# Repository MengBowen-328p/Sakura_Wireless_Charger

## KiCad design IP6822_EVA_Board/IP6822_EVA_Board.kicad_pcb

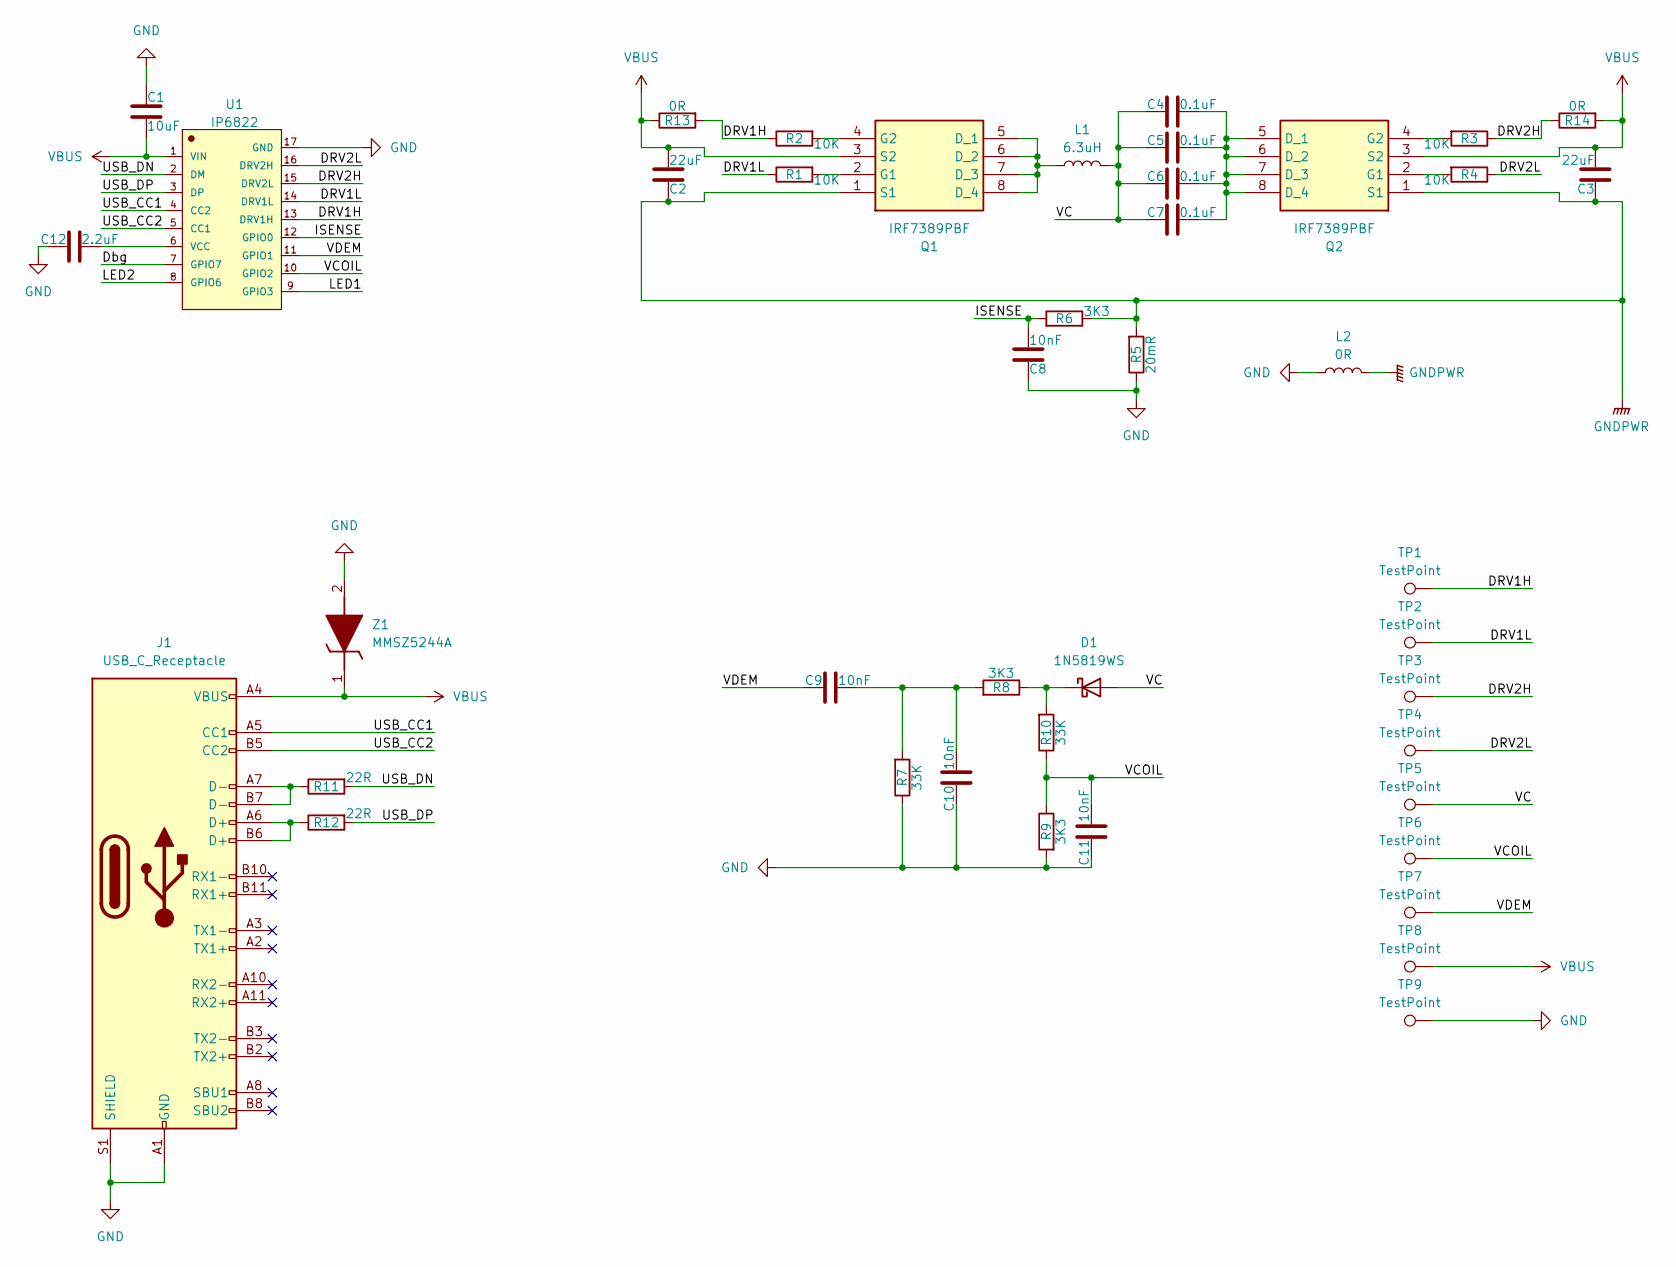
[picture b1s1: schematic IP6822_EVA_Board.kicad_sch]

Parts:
C1: 10uF; C_0603_1608Metric
C2, C3: 22uF; C_0603_1608Metric
C4, C5, C6, C7: 0.1uF; C_0805_2012Metric
C8, C9, C10, C11: 10nF; C_0603_1608Metric
C12: 2.2uF; C_0603_1608Metric
D1: 1N5819WS; D_SOD-323
J1: USB_C_Receptacle; USB_C_Receptacle_HCTL_HC-TYPE-C-16P-01A
L1: 6.3uH; L_2010_5025Metric
L2: 0R; L_0805_2012Metric
Q1, Q2: IRF7389PBF; SOIC127P600X175-8N; Manufacturer_Part_Number IRF7389PBF; Mouser Part Number 942-IRF7389PBF
R1, R2, R3, R4: 10K; R_0603_1608Metric
R5: 20mR; R_1206_3216Metric
R6, R8, R9: 3K3; R_0603_1608Metric
R7, R10: 33K; R_0603_1608Metric
R11, R12: 22R; R_0603_1608Metric
R13, R14: 0R; R_0603_1608Metric
TP1, TP2, TP3, TP4, TP5, TP6, TP7, TP8, TP9: TestPoint; TestPoint_Bridge_Pitch3.81mm_Drill1.3mm
U1: IP6822
Z1: MMSZ5244A; MMSZ5252B; Manufacturer_Part_Number MMSZ5244A

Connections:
/DRV1H: R2.1, R13.2, TP1.1, U1.13 (DRV1H)
/DRV1L: R1.1, TP2.1, U1.14 (DRV1L)
/DRV2H: R3.1, R14.1, TP3.1, U1.15 (DRV2L)
/DRV2L: R4.1, TP4.1, U1.16 (DRV2H)
/Dbg: U1.7 (GPIO7)
/ISENSE: C8.2, R6.2, U1.12 (GPIO0)
/LED1: U1.9 (GPIO3)
/LED2: U1.8 (GPIO6)
/USB_CC1: J1.A5 (CC1), U1.4 (CC2)
/USB_CC2: J1.B5 (CC2), U1.5 (CC1)
/USB_DN: R11.2, U1.2 (DM)
/USB_DP: R12.2, U1.3 (DP)
/VC: C4.1, C5.1, C6.1, C7.1, D1.2 (A), L1.2, TP5.1
/VCOIL: C11.2, R9.1, R10.1, TP6.1, U1.10 (GPIO2)
/VDEM: C9.1, TP7.1, U1.11 (GPIO1)
GND: C1.1, C8.1, C10.1, C11.1, C12.1, J1.A1 (GND), J1.A12 (GND), J1.B1 (GND), J1.B12 (GND), J1.S1 (SHIELD), L2.1, R5.1, R7.1, R9.2, TP9.1, U1.17 (GND), Z1.2 (A)
GNDPWR: C2.1, C3.1, L2.2, Q1.1 (S1), Q2.1 (S1), R5.2, R6.1
unnamed: C9.2, C10.2, R7.2, R8.2
unnamed: D1.1 (K), R8.1, R10.2
unnamed: J1.A6 (D+), J1.B6 (D+), R12.1
unnamed: J1.A7 (D-), J1.B7 (D-), R11.1
unnamed: L1.1, Q1.5 (D_1), Q1.6 (D_2), Q1.7 (D_3), Q1.8 (D_4)
unnamed: Q1.2 (G1), R1.2
unnamed: Q1.4 (G2), R2.2
unnamed: C4.2, C5.2, C6.2, C7.2, Q2.5 (D_1), Q2.6 (D_2), Q2.7 (D_3), Q2.8 (D_4)
unnamed: Q2.2 (G1), R4.2
unnamed: Q2.4 (G2), R3.2
unnamed: C12.2, U1.6 (VCC)
VBUS: C1.2, C2.2, C3.2, J1.A4 (VBUS), J1.A9 (VBUS), J1.B4 (VBUS), J1.B9 (VBUS), Q1.3 (S2), Q2.3 (S2), R13.1, R14.2, TP8.1, U1.1 (VIN), Z1.1 (K)

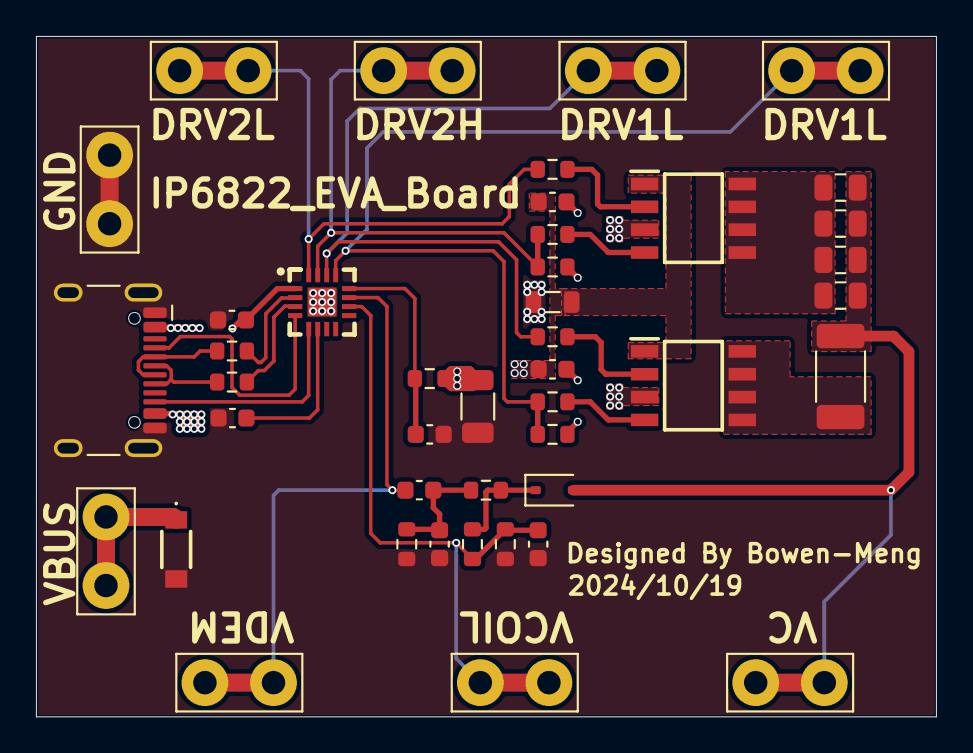
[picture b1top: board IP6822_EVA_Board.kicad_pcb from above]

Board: 2 copper layers, 50.0 x 37.8 mm, 43 parts (0 on the bottom side), 26 nets.

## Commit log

2024-10-19 Finished EVA_Board
2024-10-22 Finished IP6822 EVA Board
2024-10-22 Add EVA BOM
